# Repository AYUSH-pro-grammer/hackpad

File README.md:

# Hackpad

Hi there! Here is my personal Hack Club macropad.

It is a compact 3x3 keyboard meant for shortcuts, programming and gaming.  
The keyboard consists of a Seeed XIAO RP2040 microcontroller, OLED screen, and mechanical switches.

## Build Images

## What it includes
- 3x3 mechanical switches
- 0.91" OLED screen
- Seeed XIAO RP2040
- 3D-printed housing
- Custom PCB designed in KiCad

## Images

### Schematic

### PCB Layout

### 3D Front View

### 3D Back View

### Render 1

### Render 2

## Bill of Materials (BOM)

| Name                                    | Purpose                                | Quantity | Reference Link                                                                                                                                                                                     | Distributor               |
| --------------------------------------- | -------------------------------------- | -------- | -------------------------------------------------------------------------------------------------------------------------------------------------------------------------------------------------- | ------------------------- |
| PCB                                     | Main board for soldering all the parts | 1        | [Custom-designed PCB](https://www.lioncircuits.com/quote)                                                                                                                                                                                | Custom Fabrication        |
| Seeed XIAO RP2040                       | Main controller                        | 1        | [https://robu.in/product/seeed-studio-xiao-rp2040-v1-0/](https://robu.in/product/seeed-studio-xiao-rp2040-v1-0/)                                                                                   | Robu.in                   |
| MX Switches                             | Mechanical switches for the 3×3 keypad | 9        | [https://keychron.in/product/cherry-mx-switch-set/](https://keychron.in/product/cherry-mx-switch-set/)                                                                                             | Keychron                  |
| Keycaps                                 | Keycaps mounted on the switches        | 9        | [https://meckeys.com/shop/accessories/keyboard-accessories/keycaps/cherry-colour-pbt-keycap-set/](https://meckeys.com/shop/accessories/keyboard-accessories/keycaps/cherry-colour-pbt-keycap-set/) | Meckeys                   |
| 1N4148 Diodes                           | Prevent ghosting in the key matrix     | 9        | [https://quartzcomponents.com/products/1n4148-zener-diode](https://quartzcomponents.com/products/1n4148-zener-diode)                                                                               | Quartz Components         |
| 0.91" OLED Display (128×32 I2C SSD1306) | Displays status and information        | 1        | [https://www.buydisplay.com/i2c-blue-0-91-inch-oled-display-module-128x32-arduino-raspberry-pi](https://www.buydisplay.com/i2c-blue-0-91-inch-oled-display-module-128x32-arduino-raspberry-pi)     | BuyDisplay                |
| 5 mm LED                                | Indicates device status / key presses  | 1        | [https://robu.in/product/5mm-red-led-pack-of-10/](https://robu.in/product/5mm-red-led-pack-of-10/)                                                                                                 | Robu.in                   |
| 220 Ω Resistor                          | Limits current through the LED         | 1        | [https://robocraze.com/products/220-ohm-resistor-pack-of-10](https://robocraze.com/products/220-ohm-resistor-pack-of-10)                                                                           | RoboCraze                 |
| 3D Printed Case                         | Encloses and protects the device       | 1        | Custom-designed and 3D printed                                                                                                                                                                     | Local 3D Printing Service |

## Project files structure
- `kicad/` - PCB files
- `cad/` - 3D models
- `grb/` - gerber files for manufacturing
- `image/` - screenshots and renders

## Parts list
- 9x MX-style switches
- 9x keycaps
- 1x Seeed XIAO RP2040
- 1x 0.91" OLED screen
- 9x diodes
- 1x custom PCB
- 1x 3D-printed housing

## Firmware
For firmware I used CircuitPython.

### Brief steps
1. Load CircuitPython on the XIAO RP2040
2. Move necessary libraries onto the board
3. Upload `code.py` file 
4. Connect and test the switches

## Images
The images with PCB and 3D render can be found in the `image/` folder.

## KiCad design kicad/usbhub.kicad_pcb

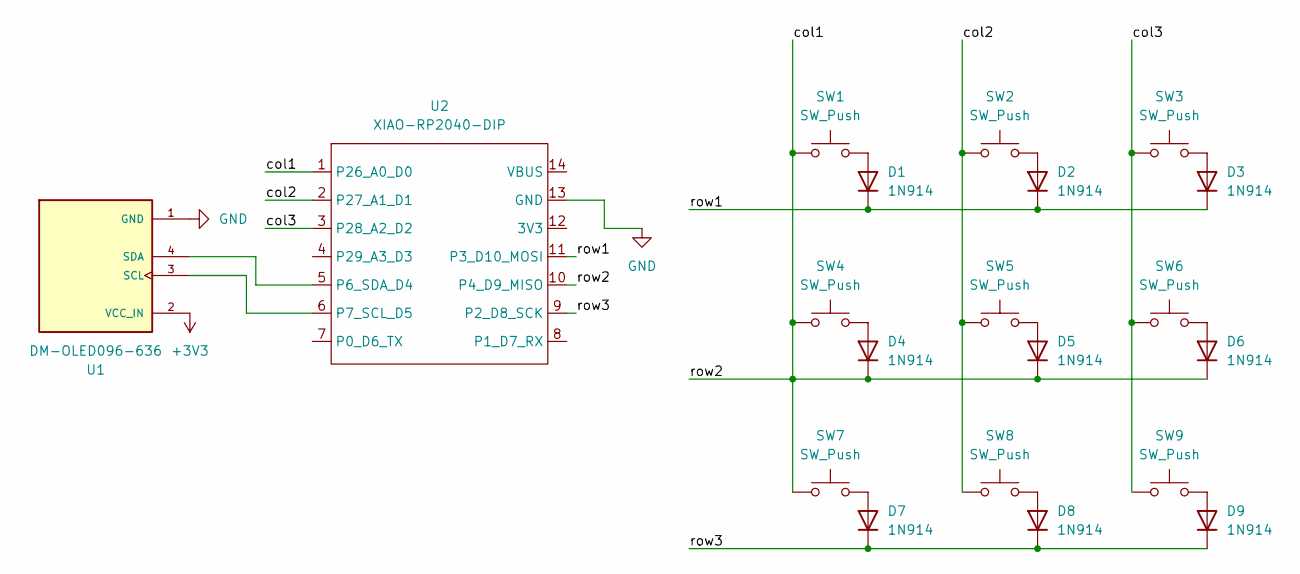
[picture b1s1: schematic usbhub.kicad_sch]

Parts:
D1, D2, D3, D4, D5, D6, D7, D8, D9: 1N914; D_DO-35_SOD27_P7.62mm_Horizontal
SW1, SW2, SW3, SW4, SW5, SW6, SW7, SW8, SW9: SW_Push; SW_Cherry_MX_1.00u_PCB
U1: DM-OLED096-636; MODULE_DM-OLED096-636; PARTREV 2018-09-10
U2: XIAO-RP2040-DIP

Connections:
+3V3: U1.2 (VCC_IN)
/col1: D4.1 (K), D5.1 (K), D6.1 (K), SW1.1, SW4.1, SW7.1, U2.1 (P26_A0_D0), U2.10 (P4_D9_MISO)
/col2: SW2.1, SW5.1, SW8.1, U2.2 (P27_A1_D1)
/col3: SW3.1, SW6.1, SW9.1, U2.3 (P28_A2_D2)
/row1: D1.1 (K), D2.1 (K), D3.1 (K), U2.11 (P3_D10_MOSI)
/row3: D7.1 (K), D8.1 (K), D9.1 (K), U2.9 (P2_D8_SCK)
GND: U1.1 (GND), U2.13 (GND)
unnamed: D1.2 (A), SW1.2
unnamed: D2.2 (A), SW2.2
unnamed: D3.2 (A), SW3.2
unnamed: D4.2 (A), SW4.2
unnamed: D5.2 (A), SW5.2
unnamed: D6.2 (A), SW6.2
unnamed: D7.2 (A), SW7.2
unnamed: D8.2 (A), SW8.2
unnamed: D9.2 (A), SW9.2
unnamed: U1.3 (SCL), U2.6 (P7_SCL_D5)
unnamed: U1.4 (SDA), U2.5 (P6_SDA_D4)

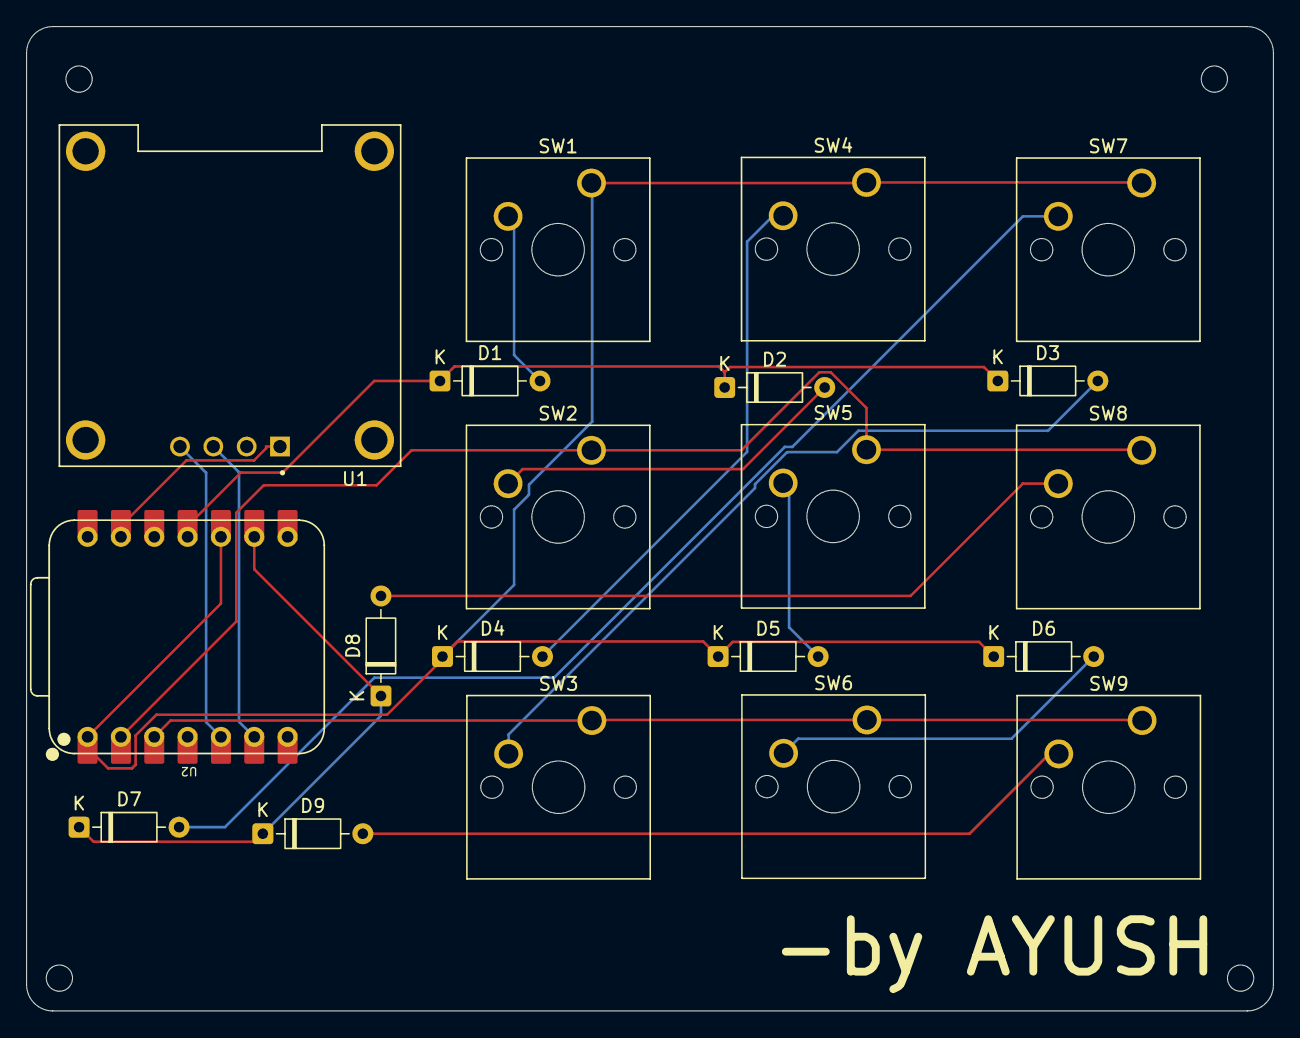
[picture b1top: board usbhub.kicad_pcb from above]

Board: 2 copper layers, 95.0 x 75.0 mm, 20 parts (0 on the bottom side), 17 nets.

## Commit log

2026-06-19 updated file
2026-06-19 added image
2026-06-20 Update Bill of Materials with references and links
2026-06-22 f3d added
